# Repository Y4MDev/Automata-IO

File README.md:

# Automata-IO
PIC microcontroller based dev board / Tarjeta de desarrollo basada en microcontroladores PIC.

This is a Test Board Based on PIC18f2550/PIC18F25K50.

Includes:

2 LEDs.
2 Push Buttons.
Acces to all IO PINs.

Beta version... Working in progress.

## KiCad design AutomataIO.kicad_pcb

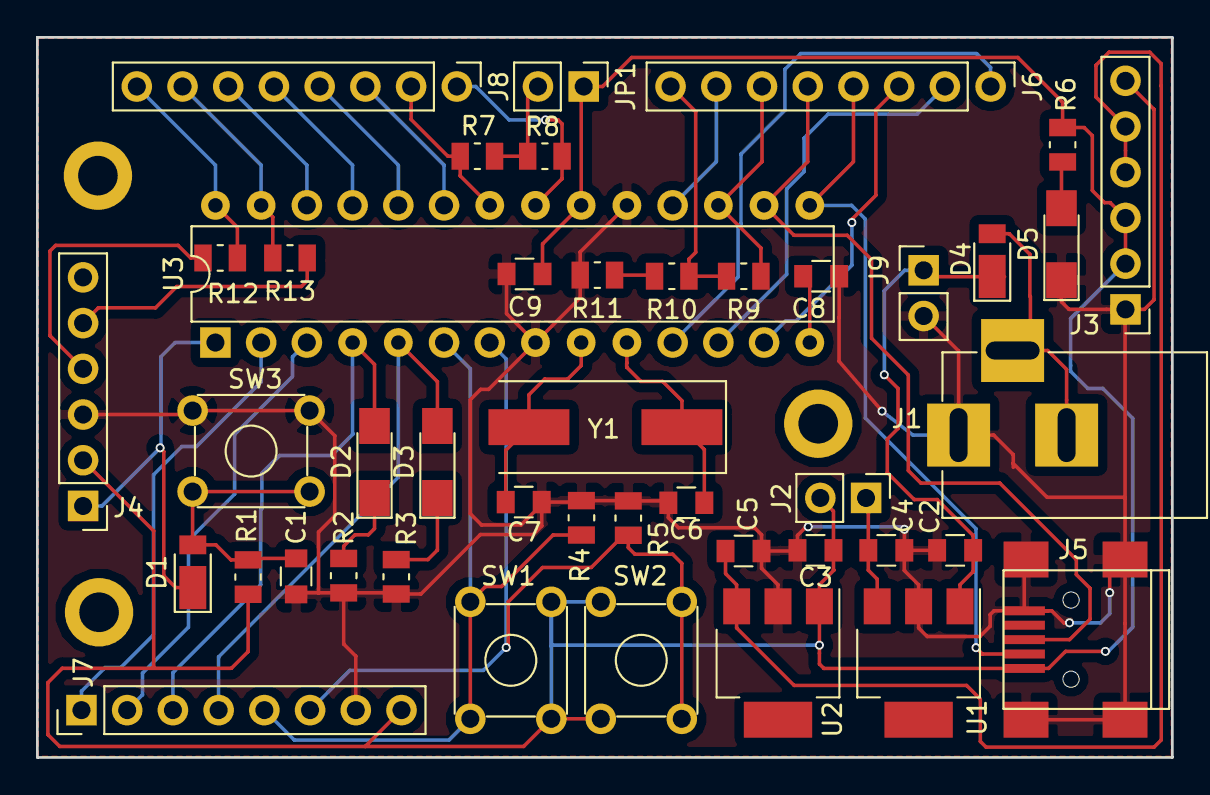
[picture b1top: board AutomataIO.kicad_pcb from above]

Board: 2 copper layers, 63.1 x 40.0 mm, 44 parts (0 on the bottom side), 40 nets.

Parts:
C1, C4, C5: 0.1uF; C_0805
C2, C3: 0.33uF; C_0805
C6, C7, C8: 22pF; C_0805
C9: 1uF; C_0805
D1: D_Schottky; D_PowerDI-123
D2: RA2_LED; LED_1206_HandSoldering
D3: RA3_LED; LED_1206_HandSoldering
D4: D_Small; D_PowerDI-123
D5: PWR_LED; LED_1206_HandSoldering
J1: Barrel_Jack; BARREL_JACK
J2: 5V_JMPR; Pin_Header_Straight_1x02_Pitch2.54mm
J3: Power Port; Pin_Header_Straight_1x06_Pitch2.54mm
J4: ICSP; Pin_Header_Straight_1x06_Pitch2.54mm
J5: USB_OTG; USB_Mini-B
J6: PORT C; Pin_Header_Straight_1x08_Pitch2.54mm
J7: PORT A; Pin_Header_Straight_1x08_Pitch2.54mm
J8: PORT B; Pin_Header_Straight_1x08_Pitch2.54mm
J9: +7VCC_INPUT; Pin_Header_Straight_1x02_Pitch2.54mm
JP1: PULL-UP RES; Pin_Header_Straight_1x02_Pitch2.54mm
R1, R4, R5, R9, R10, R11, R12, R13: 10K; R_0805_2012Metric
R2, R3, R6: 1K; R_0805_2012Metric
R7, R8: 4.7K; R_0805_2012Metric
SW1: SW1; SW_TH_Tactile_Omron_B3F-10xx
SW2: SW2; SW_TH_Tactile_Omron_B3F-10xx
SW3: SWR; SW_TH_Tactile_Omron_B3F-10xx
U1: uA78M05; SOT-223
U2: uA78M33; SOT-223
U3: PIC18F2550-ISP; DIP-28_W7.62mm
Y1: XTAL; Crystal_SMD_HC49-SD

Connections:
+3V3: C5.1, J3.4, J3.5, U2.3
+5V: C3.1, C9.1, J2.2, J3.2, J3.3, J4.2, J5.1, J7.8, JP1.1, R1.1, R6.1, SW1.1, SW1.2, SW2.1, SW2.2, U2.1, U3.20
GNDREF: C1.2, C2.2, C3.2, C4.2, C5.2, C6.2, C7.2, C8.1, C9.2, D5.1, J1.1, J3.1, J3.6, J4.3, J5.5, J5.6, J7.7, J9.2, R2.2, R3.2, R4.2, R5.2, R11.2, SW3.3, SW3.4, U1.2, U2.2, U3.8, U3.19
MCLR/Vpp: D1.1, J4.1, U3.1
unnamed: C1.1, D1.2, R1.2, SW3.1, SW3.2
unnamed: C2.1, D4.1, J9.1, U1.1
unnamed: C4.1, J2.1, U1.3
unnamed: C6.1, U3.10, Y1.1
unnamed: C7.1, U3.9, Y1.2
unnamed: C8.2, U3.14
unnamed: D2.1, R2.1
unnamed: D3.1, R3.1
unnamed: D4.2, J1.2, J1.3
unnamed: D5.2, R6.2
unnamed: J4.4, R12.1
unnamed: J4.5, R13.1
unnamed: JP1.2, R7.1, R8.1
unnamed: R10.2, R11.1
RA0/AN0: J7.1, U3.2
RA1/AN1: J7.2, U3.3
RA2/LD1: D2.2, J7.3, U3.4
RA3/LD2: D3.2, J7.4, U3.5
RA4/SW1: J7.5, R4.1, SW1.3, SW1.4, U3.6
RA5/SW2: J7.6, R5.1, SW2.3, SW2.4, U3.7
RB0/SDA: J8.1, R8.2, U3.21
RB1/SCL: J8.2, R7.2, U3.22
RB2/INT2: J8.3, U3.23
RB3: J8.4, U3.24
RB4: J8.5, U3.25
RB5: J8.6, U3.26
RB6/PGC: J8.7, R13.2, U3.27
RB7/PGD: J8.8, R12.2, U3.28
RC0: J6.1, U3.11
RC2: J6.3, U3.13
RC4/D-: J5.2, J6.4, U3.15
RC5/D+: J5.3, J6.5, U3.16
RC6/TX: J6.8, R9.2, R10.1
RC6/TX_5V: J6.6, R9.1, U3.17
RC7/RX: J6.7, U3.18
RCI: J6.2, U3.12
